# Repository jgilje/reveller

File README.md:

# Reveller

Connect your SID-file (6581/8580) to a Raspberry Pi, BeagleBone Black or TinCan Tools Hammer - 
and listen to the beautiful un-emulated SID-music.

## Compiling
[sidplayer/](https://github.com/jgilje/reveller/tree/master/sidplayer) contains the core program. It emulates a simple C=64,
and redirects SID-IO to the chip. Build using CMake.

[sidplayer-web-backend/](https://github.com/jgilje/reveller/tree/master/sidplayer-web-backend) is a frontend for the core, allowing
clients to connect and control the more basic core. This project allows any websocket client to control the 'backend' of the sidplayer. This is a Go project.

[sidplayer-web-frontend/](https://github.com/jgilje/reveller/tree/master/sidplayer-web-frontend) This is a webfrontend for reveller communicating with the webscoket backend. built using js/html 

[qt-gui/](https://github.com/jgilje/reveller/tree/master/qt-gui) is a client for the frontend written in Qt. Build
using qmake.

## Schematics
Complete Eagle board layout and schematics is available for the Raspberry Pi 
 ([board](https://raw.githubusercontent.com/jgilje/reveller/master/docs/reveller-pi.brd),
  [schematics](https://raw.githubusercontent.com/jgilje/reveller/master/docs/reveller-pi.sch))
port. Schematics for the other ports are sadly undocumented for the moment, although the core has been ported
to the other platforms.

## Cases
* BeagleBone Black, available at http://www.thingiverse.com/thing:1019636

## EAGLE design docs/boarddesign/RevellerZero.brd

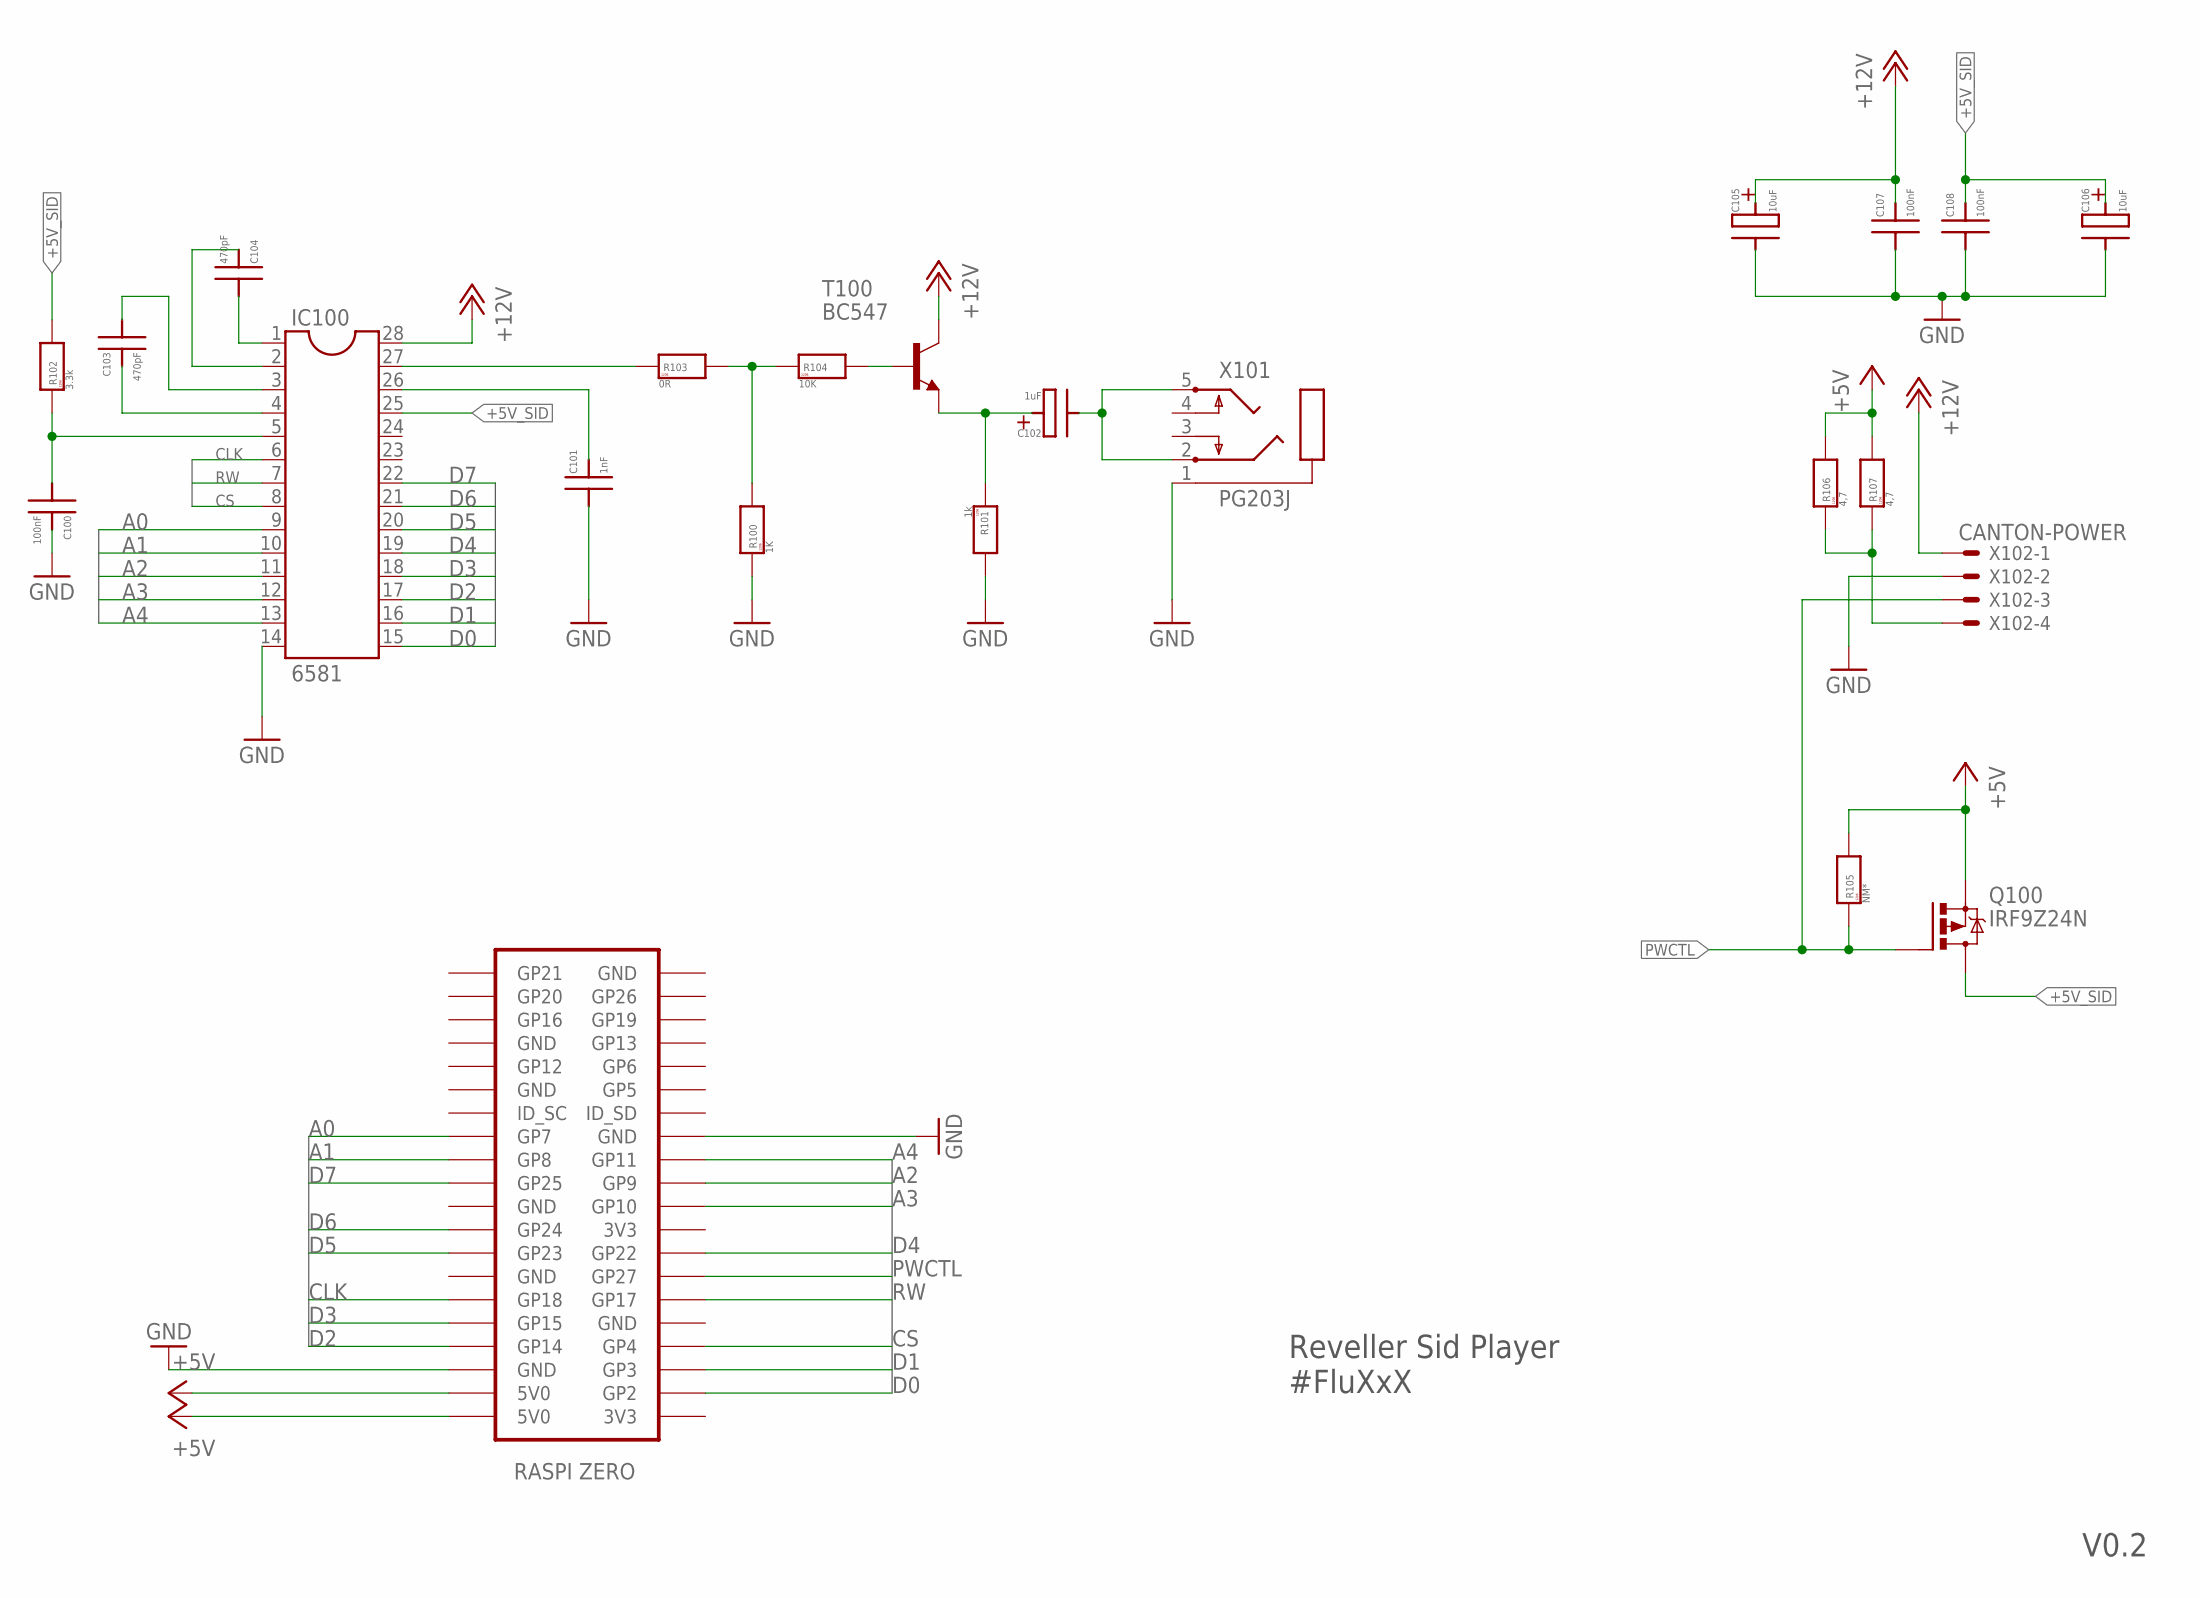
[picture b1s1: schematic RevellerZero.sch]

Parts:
C100, C107, C108: 100nF; SMD-IPC_C1206
C101: 1nF; SMD-IPC_C1206
C102: 1uF; PXE-H
C103, C104: 470pF; SMD-IPC_C1206
C105, C106: 10uF; SMD-IPC_CT7343
IC100: 6581; DIL28-6
Q100: IRF9Z24N; TO220BV
R100: 1K; SMD-IPC_R1206
R101: 1k; SMD-IPC_R1206
R102: 3.3k; SMD-IPC_R1206
R103: 0R; SMD-IPC_R1206
R104: 10K; SMD-IPC_R1206
R105: NM*; SMD-IPC_R1206
R106, R107: 4,7; SMD-IPC_R1206
T100: BC547; TO92
U$1: ZERO
X101: PG203J
X102: CANTON-POWER; 22-23-2041

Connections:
+5V: Q100.S, R105.2, R106.2, R107.2, U$1.2 (5V0), U$1.4 (5V0)
+5VEZ: R106.1, R107.1, X102.4
+5V_SID: C106.+, C108.+ (2), IC100.25, Q100.D, R102.2
+12V: C105.+, C107.+ (2), IC100.28, T100.3 (C), X102.1
A0: IC100.9, U$1.26 (GP7)
A1: IC100.10, U$1.24 (GP8)
A2: IC100.11, U$1.21 (GP9)
A3: IC100.12, U$1.19 (GP10)
A4: IC100.13, U$1.23 (GP11)
AUDIO_DC: C102.+, R101.1, T100.1 (E)
AUDIO_OUT: C102.-, X101.2, X101.5
AUDIO_PREAMP: R100.2, R103.2, R104.1
AUDIO_PREAMP_B: R104.2, T100.2 (B)
AUDIO_RAW: IC100.27, R103.1
CAP1A: C104.- (1), IC100.1
CAP1B: C104.+ (2), IC100.2
CAP2A: C103.- (1), IC100.3
CAP2B: C103.+ (2), IC100.4
CAPX: C101.+ (2), IC100.26
CLK: IC100.6, U$1.12 (GP18)
CS: IC100.8, U$1.7 (GP4)
D0: IC100.15, U$1.3 (GP2)
D1: IC100.16, U$1.5 (GP3)
D2: IC100.17, U$1.8 (GP14)
D3: IC100.18, U$1.10 (GP15)
D4: IC100.19, U$1.15 (GP22)
D5: IC100.20, U$1.16 (GP23)
D6: IC100.21, U$1.18 (GP24)
D7: IC100.22, U$1.22 (GP25)
GND: C100.+ (2), C101.- (1), C105.-, C106.-, C107.- (1), C108.- (1), IC100.14, R100.1, R101.2, U$1.6 (GND), U$1.25 (GND), X101.1, X102.2
PWCTL: Q100.G, R105.1, U$1.13 (GP27), X102.3
RESET: C100.- (1), IC100.5, R102.1
RW: IC100.7, U$1.11 (GP17)

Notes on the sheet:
Reveller Sid Player #FluXxX
V0.2

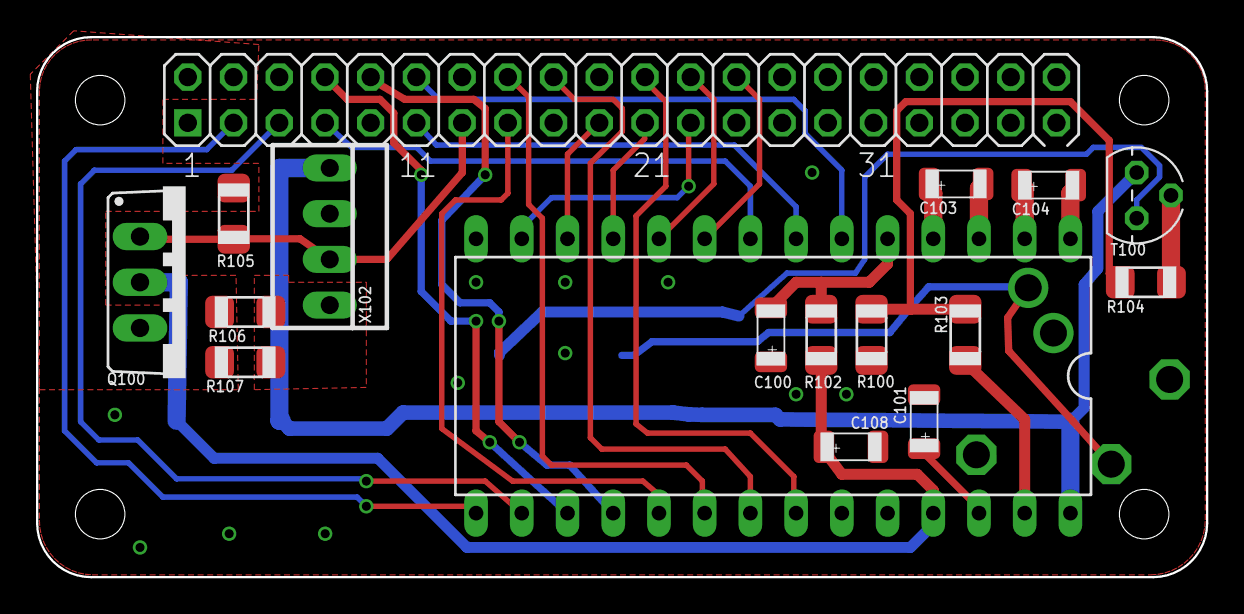
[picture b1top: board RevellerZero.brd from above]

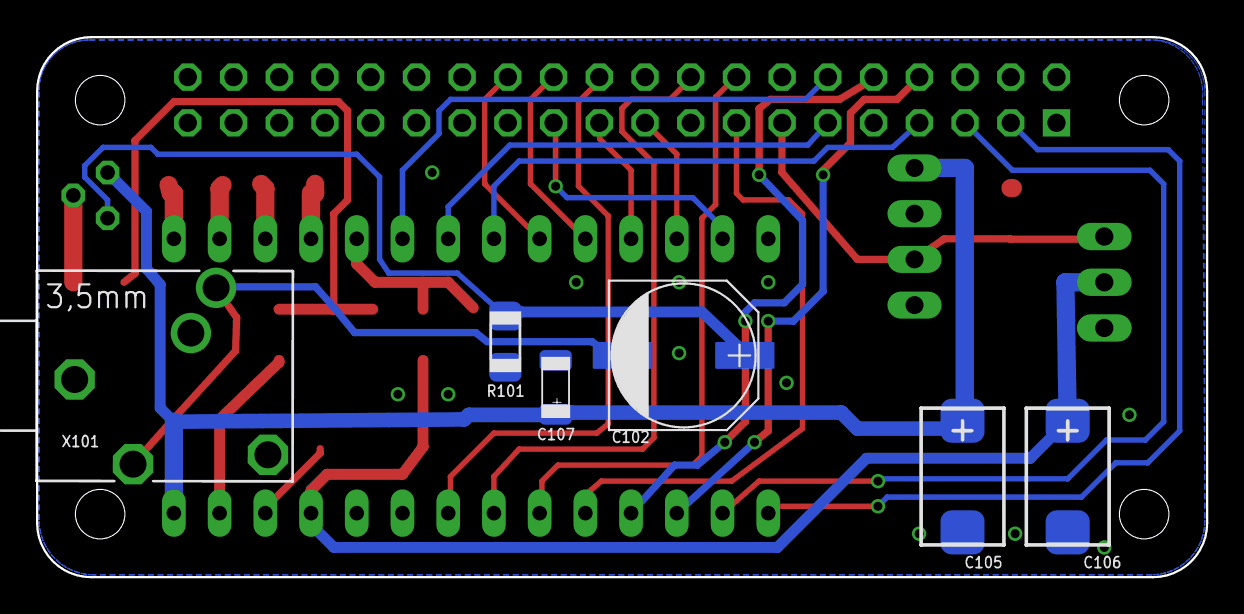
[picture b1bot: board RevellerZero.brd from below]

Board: 2 copper layers, 65.0 x 30.0 mm, 23 parts (6 on the bottom side), 33 nets.

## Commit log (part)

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2011-10-02 initial
2011-10-02 build dirs
2011-10-04 fixes after testing output from GPIO with a scope
2011-10-08 fix loading of sids not started on zero offset
2011-10-09 debug line cleanup
2011-10-18 lcd implemented started refactoring of timing-code
2011-11-07 config files for hammer
2011-11-07 gitignore
2011-11-08 collected all register writes in a single struct
2011-11-08 vic reset implementation
2011-11-08 moved wait-for-interrupt logic inside c64_play()
2011-11-14 redesigned kernel-driver around a ioctl call
2011-12-25 better cia emulation better debug (re-enabled old debug statements)
2011-12-25 removed old code to core-emulator
2011-12-25 disabled emulator time adjustment
2013-03-24 debugging for cia
2013-03-24 -Wall when compiling
2014-06-22 defined missing function calls
2014-06-22 missing include
2014-06-22 RPi port, investigating IRQ#32 disables caused by GPIO writes
2014-06-27 first actual working version :)
2014-06-27 refactored, common cli code
2014-06-28 removed compiler warnings, reverted GPIO input
2014-07-01 refactored solution, moving towards platform dependent implementations
2014-07-01 use common console-interface fir sidplayer-hammer.c
2014-07-01 cleaned up unused codebits
2014-07-14 early checkin for qt gui
2014-07-14 ignore user-files
2014-07-14 removed unused code
2014-07-14 specify sidplayer from arguments
2014-07-14 crosscompiling go
2014-07-15 connectiondialog introduced, save url in prefs, forced init of siditem type
2014-07-15 set rootpath from arguments
2014-07-16 parse sidfiles in controller
2014-07-17 moved all code belonging to sidplayer to it's own folder, enabled -Wall on c64emu
2014-07-17 log to stderr before exiting, refactored c64_debug => platform_debug
2014-07-17 flush outputs
2014-07-17 parse iso-8859-1 strings in sidfiles
2014-07-17 aligned author
2014-07-19 lsReply returns the path of it's contents
2014-07-31 don't force IOport setting
2014-07-31 install driver in free pages as marked by SID file
2014-07-31 added BASIC ROM, ROMs are now static in .c file
2014-07-31 compiler complained about undefined return result
2014-07-31 ROM files, most common versions according to online sources
2014-07-31 really simple bin-to-hex converter
2014-07-31 prev/next functions, state handling
2014-07-31 execute bit
2014-09-10 apache2 license
2014-09-10 removed non-existing header endian.h
2014-09-10 removed compile warning in vicRead
2014-09-10 u_int_32 => uint_32
2014-09-10 removed unused headers
2014-09-13 removed unnecessary unistd.h
2014-09-13 implemented an emulating windows version
2014-09-13 implemented platform_sleep for windows
2014-09-13 unistd header on unix
2014-09-13 fetch current header
2014-09-13 removed debug code
2014-09-13 initial BBB SID Cape wiring info
2014-09-13 BeagleBone Black: WIP
2014-09-13 moved hammer kernel driver to subdirectory
2014-09-18 close inputSidFile if opened
2014-09-18 initialize FILE handles
2014-09-18 sanitize input to play command with arg
2014-09-18 unnecessary compare of usec
2014-09-19 check return values
2014-09-19 added stddef.h for size_t
2014-09-19 added interactive mode
2014-09-19 refactored menu_scandir, made it easier for code analysis to see that menu_data.dir_entries was not dereferencing NULL
2014-09-22 Reveller-Pi Eagle Schematics
2014-10-01 CIA SDR emulation (return stored data)
2014-10-01 fetchOP calls loadMem now
2014-10-01 run installSIDDriver only in PSID files, SIDDriver fetches IOPort result from running init
2014-10-01 when aborting on CIA R/W, report which chip
2014-10-01 store SID writes
2014-10-05 support sprite enable (ignored)
2014-10-05 dummy support for more registers, simple SDR register handling
2014-10-05 PSID files uses SID Driver as IRQ routine
2014-10-05 split interpretMain NMI/IRQ detection - allow NMI, check reg.p for FLAG_I before triggering IRQ
2014-10-05 unnecessary debug info
2014-10-06 splitted init interpreter to new function which handles nested IRQs. don't reset stack pointer when triggering IRQ/NMI. use RTI in SIDDriver. fetch SIDDriver fetches IOport from playAddress
2014-10-09 busy loop while writing, until further debugging
2014-10-09 clear RESET after init
2014-10-09 promoted pwm_tbcnt to am335x_registers
2015-01-19 enable output on POWER-pin
2015-03-23 updated schematics
2015-03-25 enabled power control
2015-03-25 don't seek directly on inputfile, use parseHeader instead
2015-03-26 removed mistaken D7 connection to pin 20, switched rpi header gnd to gnd-symbol, switched capacitors to 2.5x5
2015-04-07 Cleaned
2015-04-09 Revised boarddesign and schmatic for better powercontrol
    Cleaned up the board with, everything done by Morten Leikvoll.
2015-04-10 More revisions...
2015-04-13 Add C64icon.png
2015-04-15 Changed from holemounted caps and res to SMDs
    Changed to get a better board design, Morten Leikvoll did all of this
    because he ment he would look more nice with some of the caps and res.
    on the backside og the board.
2015-05-06 Changed schmatic to allow for "stereo" sound
    Used wrong pinout on jack connector, thereby giving only mono sound.
    Also added one 1000uF capacitor to allow for bad powersupplys to not
    kill the raspberrypi during startup of sidchip
2015-05-08 set icon on launch
2015-05-10 CONFIG c++11 and silent
2015-05-10 set default song after load-event from server
2015-05-10 enabled poweron / poweroff for raspberry pi, with compat. for both rev1 and rev2 boards
2015-05-22 ignore C64Music
2015-05-22 build tweaks for OSX
2015-05-22 inital commit web frontend
2015-05-22 Added gruntfile.js contents
2015-05-22 dependencies for frontend
2015-05-22 class for handling communications on the websocket
2015-05-22 remove console.logs
2015-05-22 hooked up reveller react component to its root element
2015-05-22 reenabled platform executables
2015-05-23 render directories to the DOM
2015-05-23 now shows sidfiles and back button implemented
2015-05-23 added search functionality
2015-05-29 set window title
2015-06-07 fixed addr string
2015-10-14 initial checkin - android app
2015-10-14 refactored to use default-constructor, as recommmended by studio
2015-10-14 scroll to top when opening folder
2015-10-14 set ROOT-tab-path correctly
2015-10-20 commented active refs. to navigationdrawer
2015-10-20 fixed overlapping sid-listing with player controls at bottom
2015-10-20 added the reveller icon from @mikketeus
2016-02-21 refactorings, add, persist and remove manual entries
2016-03-29 Added boardesign for PiZero
    Boarddesign for PiZero, might be subjected to revision
2016-03-29 relocated boarddesigns
2016-05-13 converted charset to utf8
2016-05-13 declared functions static
2016-05-13 WIP refactorings to reduce global symbols, and prefix the remaining globals
2016-05-14 platform refactor complete
2016-05-14 pause/resume volume when not playing
2016-06-12 Added box design and revised RevellerZero design
    Raspberry Pi Rev B box design to allow for reveller HAT. Can be printed
    with or without vented design. Designed in Solidworks 2016. RevellerZero
    board design was revised due to CantonPower being placed slightly off
    board.
2016-07-07 initial rpi reveller kernel module
2016-07-07 new reveller platform for kernel-backed playback
2016-07-09 use common platform for debug and abort
2016-07-09 removed, autodetected at startup
2016-07-09 makefile for kernel driver
2016-07-23 buffer before transferring data to kernel
2016-07-23 c64_play() adjusts from platform Hz to µs, removed old (and wrong) conversion from console-interface
2016-07-23 note about the c64_vic_timer.latch
2016-07-28 updated websocket package url
2016-07-29 systemd unit
2016-08-09 corrected base-adress for rpi1 pwm init
2016-08-16 Removed bloat
2016-08-19 Cleanup
    Added Fluxxx and RevellerZero markings
2016-11-06 added and implemented flush command (discards any buffered data)
2016-11-08 removed empty platform implementations as undefined struct field initializers are set to null in c99
2016-11-08 implemented poll
2016-11-12 c64_sid_pause/resume removed, refactored to a platform-dependent function
2017-09-15 identify both BCM-alias names as rpi1
2018-02-25 the devicetree node for the RPi SoC has been defined under different names. this commit adds support for the newer style names
2021-04-19 u_int32_t => uint32_t
2021-04-19 include 'header
2021-08-04 refactored kernel module, use the device-tree/of api's to fetch io adresses and irq for us. pi4 support added.
2021-08-04 handle pi4 and pi(other) differences in timer frequencies
2021-09-08 use_osc was executing non-osc values
2021-12-29 fixed up compilation on gcc10+ due to -fno-common being default
2022-09-07 removed valid Origin requirement from websocket handler
2022-09-08 searcher handles symlink rootpath
2022-09-08 ignore build artifacts
2022-09-08 remove unread variable
2022-09-08 enable power management - on/off
2022-09-08 power command from websocket
2022-09-09 better ws url
2022-09-09 handle static files
2022-09-09 add current power state to the sidplayer's state
2022-09-10 Delete sidplayer-frontend directory
    No longer being developed. Swapped out for new frontend..
2022-09-11 rename sidplayer-web => sidplayer-web-backend/
2022-09-11 Update README.md
    Added some docs about frontend
2022-10-10 initial package builder using cpack
2022-10-10 handle reveller.service in postinst/prerm/postrm phases
2023-02-25 Bump golang.org/x/net in /sidplayer-web-backend
    Bumps [golang.org/x/net](https://github.com/golang/net) from 0.0.0-20220907135653-1e95f45603a7 to 0.7.0.
    - [Release notes](https://github.com/golang/net/releases)
    - [Commits](https://github.com/golang/net/commits/v0.7.0)
    ---
    updated-dependencies:
    - dependency-name: golang.org/x/net
2023-03-03 git ignore qt build files
2023-03-03 changed ajax lib from http to https - due to whining browser
2023-03-03 Guddi update
2023-09-02 bump cmake_minimum_required accross project
2023-09-02 added dummy implementations of reveller_platform power and shutdown
2023-09-02 start in power off. automatically turn on power when playing a song. closes #12
2023-09-02 simple qt6 compile fix
2023-09-02 removed toolbars. add http:// - prefix if url doesn't include. closes #2
2023-09-02 add missing newline for power commands
2023-10-11 Bump golang.org/x/net from 0.7.0 to 0.17.0 in /sidplayer-web-backend
    Bumps [golang.org/x/net](https://github.com/golang/net) from 0.7.0 to 0.17.0.
    - [Commits](https://github.com/golang/net/compare/v0.7.0...v0.17.0)
    ---
    updated-dependencies:
    - dependency-name: golang.org/x/net
    dependency-type: direct:production
2024-08-16 make the kernel driver compatible with kernel >= 6.4
2024-08-29 load reveller kernel module on boot
2024-08-29 install module load file
    this should make systemd automaticly load reveller kernel driver
2024-08-29 added search functionality to webinterface
2024-08-31 attempt to detect closed channels when searching returns
2025-03-13 Bump golang.org/x/net from 0.23.0 to 0.36.0 in /sidplayer-web-backend
    Bumps [golang.org/x/net](https://github.com/golang/net) from 0.23.0 to 0.36.0.
    - [Commits](https://github.com/golang/net/compare/v0.23.0...v0.36.0)
    ---
    updated-dependencies:
    - dependency-name: golang.org/x/net
    dependency-type: direct:production
2026-05-20 fixed function prototypes
2026-05-20 formatting
2026-05-20 prepare for autodetection of PDSID, and added forced PDSID. set wanted chip mode from loaded SID file's header
2026-05-20 removed zeroconf module
2026-05-21 common_sid_read => dummy_sid_read
2026-05-21 removed double-jsonified
2026-05-21 switch qt build to using cmake, integrated with main build
2026-05-21 accomodate json stringify changes
2026-05-21 include the resource file
2026-05-23 change the write cycle, removed glitches from playback
